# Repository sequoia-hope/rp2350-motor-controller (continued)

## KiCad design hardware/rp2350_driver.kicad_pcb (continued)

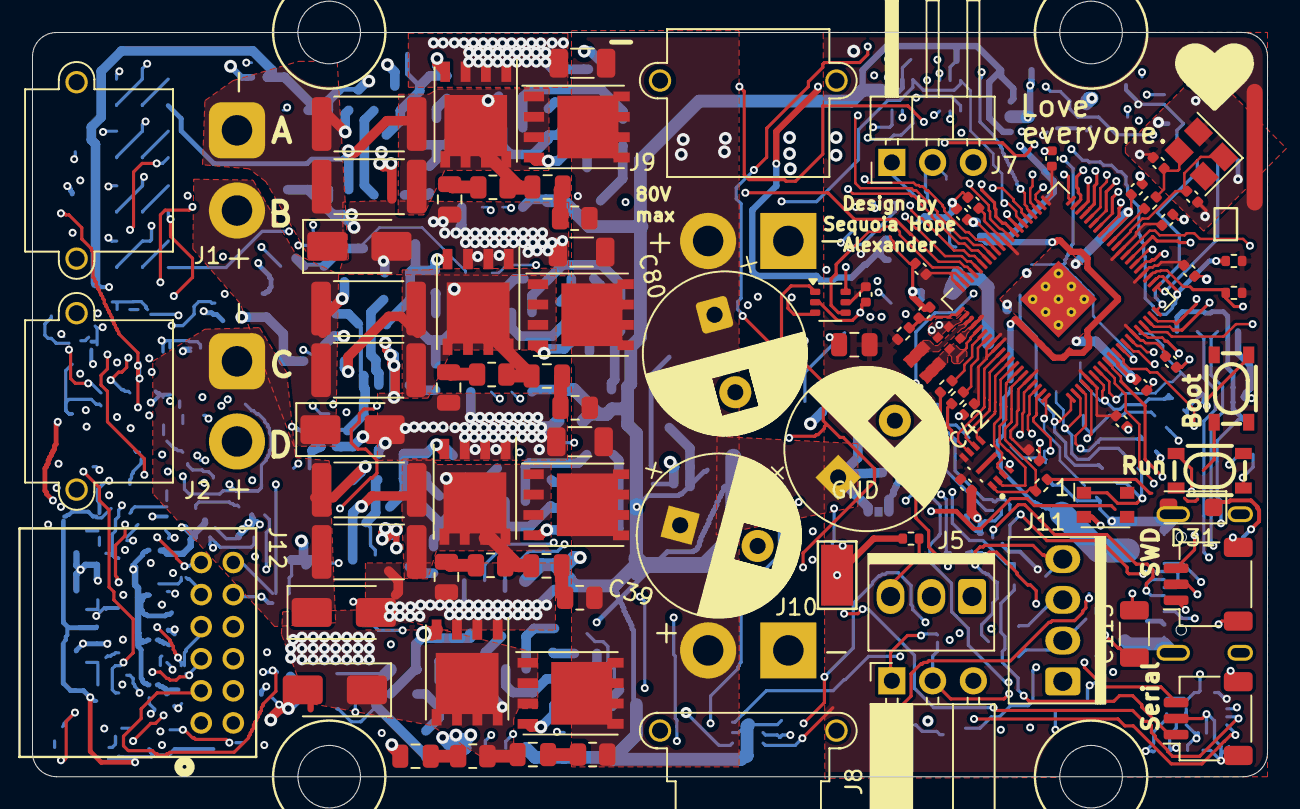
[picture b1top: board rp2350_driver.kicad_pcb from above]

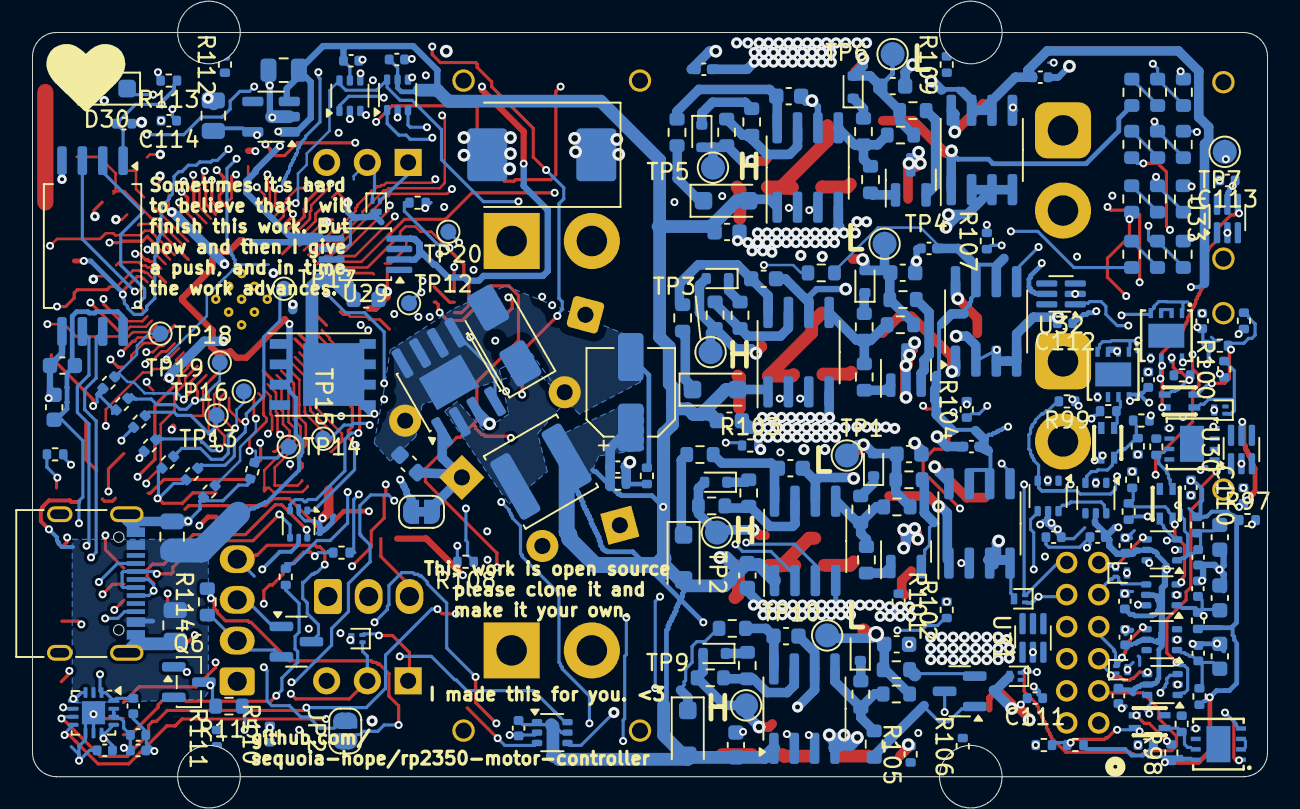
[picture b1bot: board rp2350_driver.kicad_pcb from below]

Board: 6 copper layers, 77.0 x 46.4 mm, 323 parts (229 on the bottom side), 184 nets.

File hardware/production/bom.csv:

Designator,Footprint,Quantity,Value,LCSC Part #
"AH1, AL1, BH1, BL1, CH1, CH2, CL1, CL2",PowerPAK_SO-8_123,8,MOSFETSO-8,C501507
"C1, C44, C8",1206,3,2.2uF 100V,C650969
"C10, C28, C36, C55",0603,4,10uF 35v,C194427
"C105, C106",0805,2,4.7uF 50V X5R,C98192
"C107, C108",0402,2,330pF 50V,C106206
C11,CP_Elec_5x5.4,1,100uF ±20% 10V,C191859
"C12, C47, C5",0805,3,10u 25v, C15850 
"C13, C14",0402,2,15p,C106997
"C15, C2, C27, C48, C58",0603,5,4.7uF 35V,C329940
"C16, C29, C40",0603,3,100n,C14663
"C17, C18, C21, C22, C77",0402,5,4.7u,C368809
C19,0603,1,1u,C15849
"C20, C24, C30, C32, C35, C37, C38, C4, C41, C43, C45, C46, C49, C50, C52, C59, C60, C61, C62, C63, C64, C65, C66, C71, C72, C73, C76, C79",0402,28,100n,C131394
C3,0402,1,33n,C106862
"C39, C42, C80",CP_Radial_D10.0mm_P5.00mm,3,100uF 100V,C2887236
C56,0402,1,100n,C14663
C57,0603,1,100n,
"C67, C68, C74",0402,3,47p,C20069324
C78,0603,1,1u 100v,C23829972
C81,0603,1,1uf 100v,C23829972
D1,LED_WS2812_3528_3.5x2.8mm_P1.5mm,1,WS2812B,C2890364
"D10, D14, D18, D3",D_SOD-123F,4,DSS110,C2923942
"D11, D12, D15, D16, D19, D20, D6, D7",D_SOD-523,8,CDBU0130R-HF,C2886025
"D13, D17, D21, D9",D_SMA,4,SMAJ51A,C366557
D22,SOT-23,1,ESDCAN24-2BLY,C5158050
"D23, D24, D25, D26, D27, D28, D29",SOT-883,7,5V TVS,C552559
D4,D_SMA,1,SS210,C14996
D5,D_SMC,1,SMDJ85A,C2990214
"FL1, FL2, FL3, FL4",FILTER-SMD_4P-L2.0-W1.2-BL_DLW21H,4,DLW21SN900SQ2L,C97856
"J1, J2, J9",AMASS_XT30PW-M_1x02_P2.50mm_Horizontal,3,XT30,C431092
J10,AMASS_XT30PW-F_1x02_P2.50mm_Horizontal,1,Power Output,C2913282
J11,PINREX-744-81-04TW00 _1x04_P2.54mm_Vertical,1,CAN2 PLUG,C2982033
J12,CONN12_5018761240_MOL,1,Conn_01x06,C493440
J3,USB_C_Receptacle_XKB_U262-16XN-4BVC11,1,USB_C_Receptacle_USB2.0,C2835315
"J4, J6",JST_SH_SM03B-SRSS-TB_1x03-1MP_P1.00mm_Horizontal,2,SM03B-SRSS-TB,C2763613
J5,BOOMELE-2510-3A_1x03_P2.54mm_Vertical,1,Estop Conn,C509148
J7,PinHeader_1x03_P2.54mm_Horizontal,1,Conn_01x03,C492411
J8,PinSocket_1x03_P2.54mm_Horizontal,1,Conn_01x03,C2897385
JP1,SolderJumper-2_P1.3mm_Bridged_RoundedPad1.0x1.5mm,1,Jumper_2_Open,
L2,L_pol_2016,1,3.3u,C42411119
L3,L_APV_ANR5045,1,47uH 1A,C520357
"Q1, Q2, Q3, Q4",SOT-23,4,Q_PNP_BEC,C686646
Q5,SOT-89-3,1,Q_NMOS_GDS,C7422896
"R1, R2, R21, R22, R35, R36, R49, R65, R66",0603,9,10k,C25804
"R10, R11, R27, R29, R42, R44, R74, R76",0603,8,0R,C21189
"R12, R28, R43, R53, R54, R75",0603,6,100R,C22775
"R13, R14, R15, R30, R31, R33, R45, R46, R47, R77, R78, R79",0603,12,10.2R,C2933129
"R20, R23, R39, R40, R55, R56",2512,6,8mΩ,C2904240
"R24, R26, R34, R8",0402,4,1k,C11702
"R25, R41, R73, R9",0603,4,4.7R,C2907035
R32,0402,1,33R,C25105
"R5, R57, R58, R86, R87, R88, R89, R90, R91, R92, R93, R94, R95, R96",0402,14,10k,C60490
"R50, R51",0402,2,27,C25100
"R59, R60, R62, R63, R67, R68, R70, R71",0603,8,50k 0.1%,C861451
R6,0402,1,3.3k,C2909345
"R61, R64, R69, R72",0603,4,5.1k 0.1%,C122969
R82,0402,1,100R,C106232
"R83, R84, R85",0402,3,100R 0402,C106232
"SW1, SW2",KEY-SMD_4P-L4.2-W3.2-P2.20-LS4.6,2,Button,C19724063
TH1,0603,1,Thermistor 10k,C13564
TP8,TestPoint_Keystone_5019_Minature,1,TestPoint,C238130
"U1, U12, U6, U7",SOIC-8_3.9x4.9mm_P1.27mm,4,EG3113,C480666
"U10, U5, U9",SOIC-8_3.9x4.9mm_P1.27mm,3,INA240A1D,C1346458
U101,WQFN-14-1EP_2.5x2.5mm_P0.5mm_EP1.45x1.45mm,1,FUSB302BMPX,C442699
U11,SOT-666,1,USBLC6-2P6,C2827693
"U13, U14, U15, U17, U22, U23, U24, U25, U26, U27",SOT-363_SC-70-6,10,TS5A3159DCK,C46388
U16,SOIC-8_7.5x5.85mm_P1.27mm,1,CA-IS3052CG,C41784142
"U18, U19, U20, U21",DFN-8_L3.0-W3.0-P0.65-BL-EP,4,SIT3088ETK,C601076
U28,SOIC-8-1EP_3.9x4.9mm_P1.27mm_EP2.29x3mm,1,XL7005A,C50848
U29,SOT-23-6,1,LM74700,C2941042
U3,IC_W25Q16JVUXIQ_TR,1,W25Q16JV,C2843335
U4,SOT-23-5,1,SPX3819M5-L-3-3,C20617301
U8,RP2350-QFN-80-1EP_10x10_P0.4mm_EP3.4x3.4mm_ThermalVias,1,RP2350_80QFN,C42415655
Y1,Crystal_SMD_3225-4Pin_3.2x2.5mm,1,ABM8-272-T3,C20625731

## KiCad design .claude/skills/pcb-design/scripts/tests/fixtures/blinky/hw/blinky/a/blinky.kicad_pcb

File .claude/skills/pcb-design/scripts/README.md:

# Check scripts

The automated checks the gates rely on. Paste a check's summary into the gate
file; every script exits non-zero on failure and can write the findings as JSON
with `--json`. Paths below are from the project root.

```sh
S=.claude/skills/pcb-design/scripts
python3 $S/nets_check.py hw/main/a             # phase 3
python3 $S/nets_check.py hw/main/a --rules     # phase 5 on
python3 $S/nets_check.py hw/main/a --rules --routed   # phase 7 on: length_limit, "no vias"
python3 $S/sync_check.py hw/main/a             # phase 6 on; add --bom/--cpl at release
python3 $S/silk_check.py hw/main/a             # phase 9
python3 $S/jlc_parts.py show C1525 C97521      # phase 1 and 10: stock, basic/extended, lifecycle
python3 $S/schematic_style_check.py hw/main/a  # phase 2
python3 $S/placement_check.py hw/main/a        # phase 6
python3 $S/transplant.py ref.kicad_pcb hw/main/a/main.kicad_pcb --anchor U1=U1 ...   # phase 6: copy a vendor block
python3 $S/autoroute.py hw/main/a --planes In1.Cu,In2.Cu    # phase 7: ultraroute, governed, judged by KiCad
python3 $S/stitch.py hw/main/a --net GND --pads 'C*' --pads U3:6 --tag padvias --lock   # phase 7, before routing
python3 $S/stitch.py hw/main/a --net GND --net +3V3 --grid 1.6 --fix   # phase 7: stitching vias
python3 $S/render.py hw/main/a design/renders    # every visual gate: top/bottom/layers/3D/assembly/schematic
.venv/bin/python $S/gerber_render.py hw/main/a/fab/gerbers design/renders/gerbers   # phase 10 (pip install gerbonara)
```

| Priority | Script | Status | Used at | Catches |
|----------|--------|--------|---------|---------|
| 1 | `sync_check.py` | **done** | 6–10 | schematic / PCB / BOM / CPL mismatches in presence, value, footprint, every user field (MPN, LCSC, ...), DNP and exclude-from-BOM; built parts missing a required field |
| 2 | `silk_check.py` | **done** | 9 | silk overlaps, silk on pads/edge (KiCad DRC, forced on), silk text over tented vias, missing pin-1 / polarity marks, designators hidden, under a part, or nearer another part, too many rotations, small text, unlabeled connectors, missing board identity |
| 3 | `nets_check.py` | **done** | 3, 5 | nets missing from `nets.csv` (both directions), bad classes, missing reasons; derives widths (IPC-2152), via counts, clearances (IPC-2221); with `--rules`, checks KiCad net classes match and cover them; with `--routed`, routed length against `length_limit` and "no vias" rows |
| — | `jlc_parts.py` | **done** | 1, 10 | JLC part search; stock, basic/extended and lifecycle per LCSC number; datasheet download (LCSC, then wget) and `sources.csv` re-fetch |
| 4 | `placement_check.py` | **done** | 6 | decouplers far from the pin their `Decouples` field names, crystals far from the IC, passives in rows, keep-apart pairs, parts off the board; ratsnest score |
| 5 | `schematic_style_check.py` | **done** | 2 | grid-placed symbols, labels where wires belong, rotated power/ground symbols, missing values/footprints/fields, decouplers drawn far from their pin, global labels on one sheet, overlapping text |
| — | `transplant.py` | **done** | 6 | copies a vendor layout block (parts, zones with settings, tracks, vias) relative to an anchor part; `--clip`, `--exclude`, `--tag` |
| — | `autoroute.py` | **done** | 7 | ultraroute (`vendor/ultraroute`, built by `scripts/route.sh`) on the board with its locked copper kept and plane layers marked, seeds tried in turn under the governance in routing.md; every result judged by KiCad after a refill (signal opens, errors the route added), the best kept; parts move only with `--nudge` |
| — | `stitch.py` | **done** | 7 | ground vias at decoupler and regulator pads (before routing, locked); stitching vias: a grid in the pours that keeps off silk text, one in every pour fragment, and vias for plane-net pads/tracks the router left without one; every via clear of silk text. `--pads REF:N` means N vias round REF, not pin N; pad vias ignore the regenerated "stitch" group, and with `--wired` count only a via a track joins to the pad (a net with no outer pour), so give any power pin the router may strand (a flash VCC) a pad via before routing |
| — | `render.py` | **done** | 2, 6, 7, 9, 10 | the gate renders in one command: top and bottom with the silk painted over the copper (a single KiCad plot hides silk under copper), each copper layer, 3D both sides, assembly drawing, schematic PDF |
| — | `gerber_render.py` | **done** | 10 | the gerber review outside KiCad: parses the fab gerbers and drills with gerbonara, prints objects per layer, renders each layer (headless Chrome; ImageMagick's SVG renderer blanks the silk) |
| — | `via_nudge.py` | **done** | 7 | moves unlocked router vias out from under silk text (labels that can't be reserved without blocking the router), dragging their track ends, keeping the change only if DRC gets no worse |
| 6 | `current_check.py` | spec | 7 | narrowest copper neck and via count per power net vs `nets.csv` |
| 7 | `plane_check.py` | spec | 7 | GND plane splits/slots, high-speed traces crossing them |
| 8 | `crosstalk_check.py` | spec | 8 | aggressor/victim parallel runs |
| 9 | `cpl_check.py` | spec | 10 | renders CPL overlay for rotation/pin 1 verification |

## Requirements

KiCad 9 (`kicad-cli`) for all of them; `silk_check.py` also needs KiCad's
python module (`pcbnew`). `scripts/doctor.sh` checks both.

## How they read the design

- Schematic: `kicad-cli sch export netlist` (hierarchy, annotation and DNP
  resolved by KiCad). Board: the `.kicad_pcb` S-expression, or `pcbnew` where
  geometry is needed. Shared code is in `kicad_files.py`.
- `silk_check.py` runs KiCad's DRC on a scratch copy with every silk rule
  forced to error, so a rule set to "ignore" in the project can't hide an
  overlap, and DRC exclusions still count.
- Thresholds live in `design/checks.toml`; defaults are in
  `kicad_files.DEFAULTS`. Loosen a value there with a comment giving the
  reason, and log it in `decisions.md`.

## Writing KiCad files

`kicad_write.py` does the two things `kicad-cli` can't:

- `Schematic`: place library symbols, wires, labels and power symbols at
  coordinates you planned, and save a `.kicad_sch`. On save it splits wires
  at every T and adds junctions, as the editor would (KiCad leaves a pin or
  junction in the middle of a wire unconnected).
- `update_pcb(sch, pcb)`: Update PCB from Schematic, headless. Footprints,
  fields, DNP/BOM flags and pad nets come from the schematic; parts already
  on the board keep their position.

Always follow a write with `kicad-cli sch erc` and a look at the exported PDF.

## Tests

```sh
cd .claude/skills/pcb-design/scripts/tests
python3 make_fixture.py     # builds fixtures/blinky, a 3-part board that passes everything
python3 test_checks.py      # each rule: the fixture passes, a copy broken in one way fails
```

A new rule gets a pass case and a fail case here before it is used at a gate.

## Next

The remaining scripts follow the same pattern: a `kicad_files` loader, a
`Report`, thresholds from `checks.toml`, and a broken copy of the fixture per
rule. `placement_check.py` is next, since placement is where the most
babysitting happens.

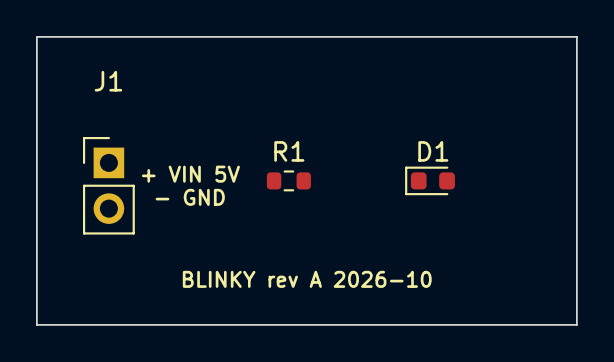
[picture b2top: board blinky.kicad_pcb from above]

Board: 2 copper layers, 30.0 x 16.0 mm, 3 parts (0 on the bottom side), 3 nets, no tracks yet.

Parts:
D1: RED; LED_0603_1608Metric
J1: VIN; PinHeader_1x02_P2.54mm_Vertical
R1: 1k; R_0603_1608Metric

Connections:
/LED_A: D1.2, R1.2
/VIN: J1.1, R1.1
GND: D1.1, J1.2

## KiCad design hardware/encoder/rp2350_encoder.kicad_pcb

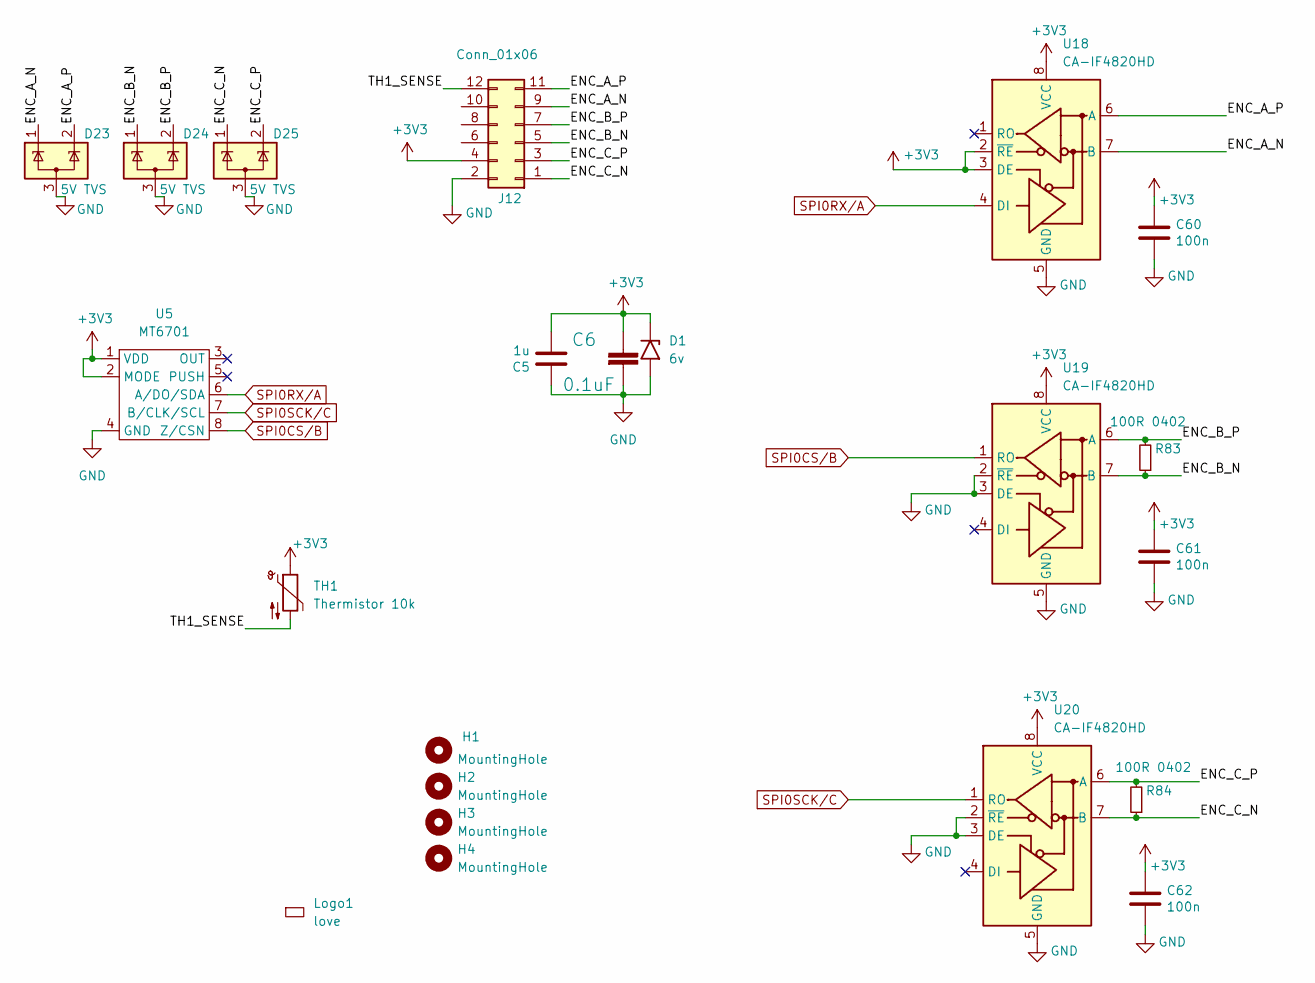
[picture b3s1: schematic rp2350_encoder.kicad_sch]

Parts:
C5: 1u; C_0603_1608Metric; LCSC C15849
C6: 0.1uF; C_0603_1608Metric; LCSC C14663
C60, C61, C62: 100n; C_0402_1005Metric; LCSC C131394
D1: 6v; D_SOD-123F; LCSC C2922753
D23, D24, D25: 5V TVS; SOT-883; LCSC C552559
H1, H2, H3, H4: MountingHole; MountingHole_3.1mm
J12: Conn_01x06; CONN12_5018761240_MOL; LCSC C493440
Logo1: love; love_small
R83, R84: 100R 0402; R_0402_1005Metric; LCSC C106232
TH1: Thermistor 10k; R_0603_1608Metric; LCSC C13564
U5: MT6701; SO-8_3.9x4.9mm_P1.27mm; LCSC C2856764
U18, U19, U20: CA-IF4820HD; DFN-8_L3.0-W3.0-P0.65-BL-EP; LCSC C6055596

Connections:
+3V3: C5.2, C6.1, C60.1, C61.1, C62.1, D1.1 (A1), J12.4, TH1.1, U5.1 (VDD), U5.2 (MODE), U18.2 (~RE), U18.3 (DE), U18.8 (VCC), U19.8 (VCC), U20.8 (VCC)
/ENC_A_N: D23.1 (K), J12.9, U18.7 (B)
/ENC_A_P: D23.2 (K), J12.11, U18.6 (A)
/ENC_B_N: D24.1 (K), J12.5, R83.1, U19.7 (B)
/ENC_B_P: D24.2 (K), J12.7, R83.2, U19.6 (A)
/ENC_C_N: D25.1 (K), J12.1, R84.1, U20.7 (B)
/ENC_C_P: D25.2 (K), J12.3, R84.2, U20.6 (A)
/TH1_SENSE: J12.12, TH1.2
GND: C5.1, C6.2, C60.2, C61.2, C62.2, D1.2 (A2), D23.3 (A), D24.3 (A), D25.3 (A), J12.2, U5.4 (GND), U18.5 (GND), U19.2 (~RE), U19.3 (DE), U19.5 (GND), U20.2 (~RE), U20.3 (DE), U20.5 (GND)
SPI0CS/B: U5.8 (Z/CSN), U19.1 (RO)
SPI0RX/A: U5.6 (A/DO/SDA), U18.4 (DI)
SPI0SCK/C: U5.7 (B/CLK/SCL), U20.1 (RO)

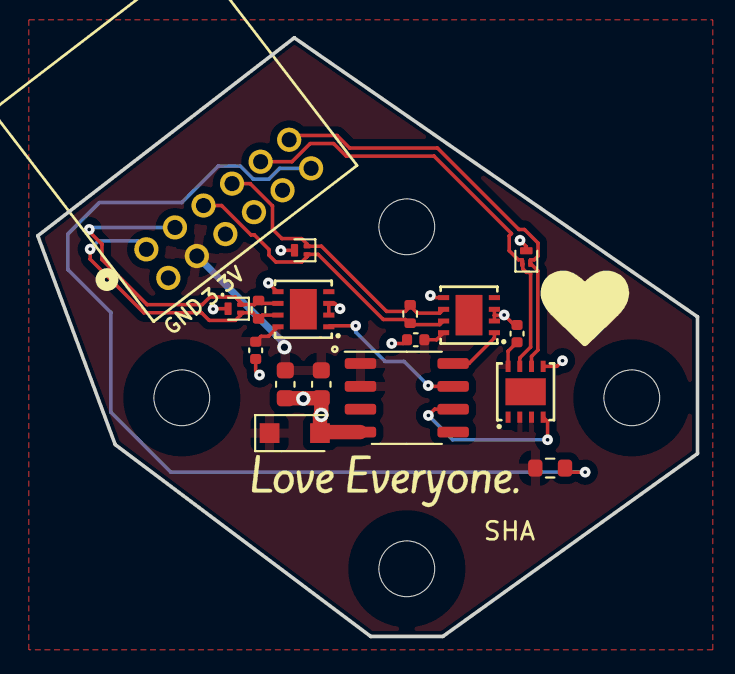
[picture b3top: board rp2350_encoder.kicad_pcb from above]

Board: 2 copper layers, 36.7 x 33.3 mm, 22 parts (0 on the bottom side), 12 nets.

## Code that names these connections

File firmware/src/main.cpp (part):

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// Board labels A/B/C are swapped vs schematic for A and C.
// PWM and current sense are consistent with each other (schematic naming),
// but the output connector labels on the board are swapped:
//   Board "A" = GPIO6/7 (schematic "C"), ADC2 (GPIO42)
//   Board "B" = GPIO4/5 (schematic "B"), ADC1 (GPIO41)
//   Board "C" = GPIO2/3 (schematic "A"), ADC0 (GPIO40)
// Pin defines use board labels since that's what you see on the hardware.
#define PIN_AH 6
#define PIN_AL 7
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#define CURRENT_SENSE_SAT_A  (CURRENT_SENSE_REF_V / (SHUNT_RESISTOR * CURRENT_AMP_GAIN))
#define CURRENT_LIMIT_MAX_A  (CURRENT_SENSE_SAT_A * 0.98f)  // just under saturation

// VMOT sensing: GPIO46 = ADC channel 6, voltage divider 100k / 5.1k
#define PIN_VMOT 46
#define VMOT_DIVIDER_RATIO (105.1f / 5.1f)  // Vmot = Vadc * ratio

// --- Bus overvoltage guard + optional brake chopper (findings F-28) ---------
// The D half-bridge is dual-role by design: 4th motor leg (stepper / second
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// fail-safe with no firmware alive. The bootstrap recharges through the
// resistor each off-period, so duty is capped below 100%.
//
// GPIO9 is D_PWM_L\ (ACTIVE LOW): its 10k pull-down holds the low FET ON.
// It must be driven HIGH before the first chop, or the chopper simply never
// conducts: the EG3113 interlocks (datasheet V1.2 §8.2 truth table — HIN=1
// with LIN\=0 gives HO=0 AND LO=0), so raising CH2 while CL2 is still
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#ifndef BRAKE_CHOPPER
#define BRAKE_CHOPPER 0            // build with -DBRAKE_CHOPPER=1 + fit the resistor
#endif
#define PIN_BRAKE_H       8        // D_PWM_H, CH2 gate (active high)
#define PIN_BRAKE_L       9        // D_PWM_L\, CL2 gate (ACTIVE LOW)
#define VBUS_GUARD_V      63.0f    // start folding back current_limit
#define VBUS_GUARD_FULL_V 66.0f    // torque ~zero here
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// Encoder power switch (U17, TS5A3159DCK)
// V_SW LOW = V_ENC outputs +3V3 (NC path)
// V_SW HIGH = V_ENC outputs Vdrive (NO path)
#define PIN_V_SW 13

// Encoder SPI (SPI0, MT6701 — auto-detected via CRC)
// GPIO16 = SPI0 RX  = MISO (data from encoder)
// GPIO17 = SPI0 CSn = chip select
// GPIO18 = SPI0 SCK = clock
#define PIN_ENC_MISO 16  // ENC_A_DATA
#define PIN_ENC_CS   17  // ENC_B_DATA
#define PIN_ENC_SCK  18  // ENC_C_DATA

// Encoder differential transceiver direction (SIT3088ETK)
// SW LOW  = receive (differential → MCU)
// SW HIGH = transmit (MCU → differential)
#define PIN_ENC_A_SW 26  // MISO direction: receive
#define PIN_ENC_B_SW 27  // CS direction: transmit
#define PIN_ENC_C_SW 28  // SCK direction: transmit

// Encoder I/O path switches (TS5A3159DCK)
// SW LOW  = NC path (differential transceiver → encoder connector)
// SW HIGH = NO path (hall sensor input)
#define PIN_H1_SW 34  // ENC_A_P routing
#define PIN_H2_SW 35  // ENC_A_N routing
#define PIN_H3_SW 36  // ENC_B_P routing

// Hall sensor pins (active when H*_SW = HIGH, directly to MCU)
#define PIN_HALL_A 31
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#define PIN_HALL_C 33

// Remaining signal-path switches
#define PIN_ENC_D_SW      29  // channel D transceiver direction
#define PIN_I2C_SW        15  // U27: ENC_B_N pin -> I2C SDA (HIGH = I2C mode)
#define PIN_EXT_ANALOG_SW 37  // U13/U14/U24/U25: ADC4/5 <- phase sense (LOW) / encoder analog (HIGH)
#define PIN_TH_SW         30  // U15: ADC7 <- board NTC (LOW) / motor thermistor (HIGH)
// Rev B: TS5A3159 in series with each 100R encoder termination (U30-U33).
// HIGH = termination in circuit (differential encoders); LOW = open, so
// single-ended signals see the 10k/10k bias as a 1.65V threshold.
// On rev A boards GPIO38 only reaches test point TP20 - driving it is harmless.
#define PIN_TERM_EN       38

// USB PD controller (FUSB302BMPX on I2C1)
#define PIN_PD_SDA  22
#define PIN_PD_SCL  23
#define PIN_PD_INT  39

// Status LED (WS2812 on GPIO11)
#define PIN_LED 11
static Adafruit_NeoPixel led(1, PIN_LED, NEO_GRB + NEO_KHZ800);

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#define LED_RUNNING()  setLED(128, 0, 255)  // purple: demo sine running
#define LED_ERROR()    setLED(255, 40, 0)   // orange: demo could not start

// Debug serial via UART0 (GPIO0 TX, GPIO1 RX) through debug probe UART bridge.
// Falls back to USB CDC if debug probe not connected.
#define PIN_UART_TX 0
#define PIN_UART_RX 1
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
// --- VMOT reading ---
// GPIO46 = ADC channel 6 on RP2350B (base GPIO 40)
#define VMOT_ADC_CHAN (PIN_VMOT - 40)
static float readVMOT() {
    RP2040ADCEngine *eng = getADCEngine();
    if (eng->initialized && eng->channelsEnabled[VMOT_ADC_CHAN]) {
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        return raw * eng->adc_conv * VMOT_DIVIDER_RATIO;
    }
    // Before DMA engine init, use one-shot analogRead (10-bit default on arduino-pico)
    return analogRead(PIN_VMOT) * (3.3f / 1024.0f) * VMOT_DIVIDER_RATIO;
}

// Forward declarations
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// V_ENC = 3.3V, transceivers receiving, hall/I2C/analog paths off,
// motor thermistor off, termination open.
static void initSwitchGpios() {
    const uint8_t sw_pins[] = {PIN_V_SW, PIN_ENC_A_SW, PIN_ENC_B_SW, PIN_ENC_C_SW,
                               PIN_ENC_D_SW, PIN_H1_SW, PIN_H2_SW, PIN_H3_SW,
                               PIN_I2C_SW, PIN_EXT_ANALOG_SW, PIN_TH_SW, PIN_TERM_EN};
    for (uint8_t p : sw_pins) {
        digitalWrite(p, LOW);
        pinMode(p, OUTPUT);
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    initSwitchGpios();
#if MOTOR_CONFIG == MOTOR_MT6701
    // Encoder 3.3V supply
    digitalWrite(PIN_V_SW, LOW);
    // Differential transceiver directions: MISO=receive, CS/SCK=transmit
    digitalWrite(PIN_ENC_A_SW, LOW);
    digitalWrite(PIN_ENC_B_SW, HIGH);
    digitalWrite(PIN_ENC_C_SW, HIGH);
    // Route to differential transceiver (NC path)
    digitalWrite(PIN_H1_SW, LOW);
    digitalWrite(PIN_H2_SW, LOW);
    digitalWrite(PIN_H3_SW, LOW);
    // Differential encoder attached: termination in circuit (rev B)
    digitalWrite(PIN_TERM_EN, HIGH);
#elif MOTOR_CONFIG == MOTOR_HALLS
    // Hall sensor Vdrive supply
    digitalWrite(PIN_V_SW, HIGH);
    // Transceivers unused for halls, all receive (safe default)
    digitalWrite(PIN_ENC_A_SW, LOW);
    digitalWrite(PIN_ENC_B_SW, LOW);
    digitalWrite(PIN_ENC_C_SW, LOW);
    // Route to hall sensor inputs (NO path)
    digitalWrite(PIN_H1_SW, HIGH);
    digitalWrite(PIN_H2_SW, HIGH);
    digitalWrite(PIN_H3_SW, HIGH);
    // Single-ended halls: termination stays open
    digitalWrite(PIN_TERM_EN, LOW);
#endif
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    // Current sense + VMOT ADC channel
    SERIAL_PORT.println("Current sense init...");
    current_sense->linkDriver(driver);
    getADCEngine()->addPin(PIN_VMOT);  // register VMOT before engine->init() runs
    // Enable phase state so calibrateOffsets() inside init() actually sees
    // 50% duty switching (not the static braking state from driver->init()).
    // Without this, _writeDutyCycle6PWM ignores the setPwm(Vs/2,...) call
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        return;
    }

    // Try all 6 permutations of (GPIO31, GPIO32, GPIO33) → (hallA, hallB, hallC)
    // Score each by net monotonic transitions (tolerates bouncing at sector boundaries)
    // SimpleFOC sector table: hall_state → sector
    //   state = (C<<2)|(B<<1)|A    sectors: {-1, 0, 4, 5, 2, 1, 3, -1}
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    Wire1.setSCL(PIN_PD_SCL);
    Wire1.begin();
    pd_ufp = new PD_UFP_Log_c();
    pd_ufp->init(PIN_PD_INT, PD_POWER_OPTION_MAX_20V);
    SERIAL_PORT.println("PD: FUSB302 initialized, requesting 20V");
#endif

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
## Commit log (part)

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2024-11-16 Initial commit, rough schematic
2024-11-19 Add 4th bridge, update connectors
2024-11-29 Refine design rules, make cpu fit rules, add gitignore
2024-11-29 adjust stackup, rotate CPU, update via and trace defaults
2024-12-02 refining layout, beginning to sort out differential encoders
2024-12-02 Add photo
2024-12-18 progress on encoder connector and differential IC selection
2025-01-19 update encoder section - multi encoder port maybe sorted
2025-01-25 All components in board footprint. Big readme update.
2025-01-25 Move board image to top of readme.
2025-07-28 100 percent routed and no DRC errors! needs massive review still.
2025-11-11 Cleaned up schematic encoder layout, fixed a sch/layout bug.
2025-11-12 Added USB-C PD, updated silk.
2025-11-14 Update schematic size, add PDF schematic.
2025-11-18 Swap ideal diode to something which supports VMOT
2025-11-18 Label credit card and business card size reference boxes
2025-11-22 bunch of small trace cleanup
2026-01-20 Silly but complete routing of the 80v power supply
2026-01-20 minor tweaks
2026-04-19 Whether inadvisedly or not, I have ordered this rev
2026-04-28 Fix a few parts as per corrections made during order.
2026-05-27 Add encoder plus updated motor driver files.
2026-05-27 Add firmware, move hardware to hardware directory.
2026-05-27 update screenshots
2026-05-27 remove incorrect max voltage silk
